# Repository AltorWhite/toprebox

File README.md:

topre ergo keyboard for my small hands

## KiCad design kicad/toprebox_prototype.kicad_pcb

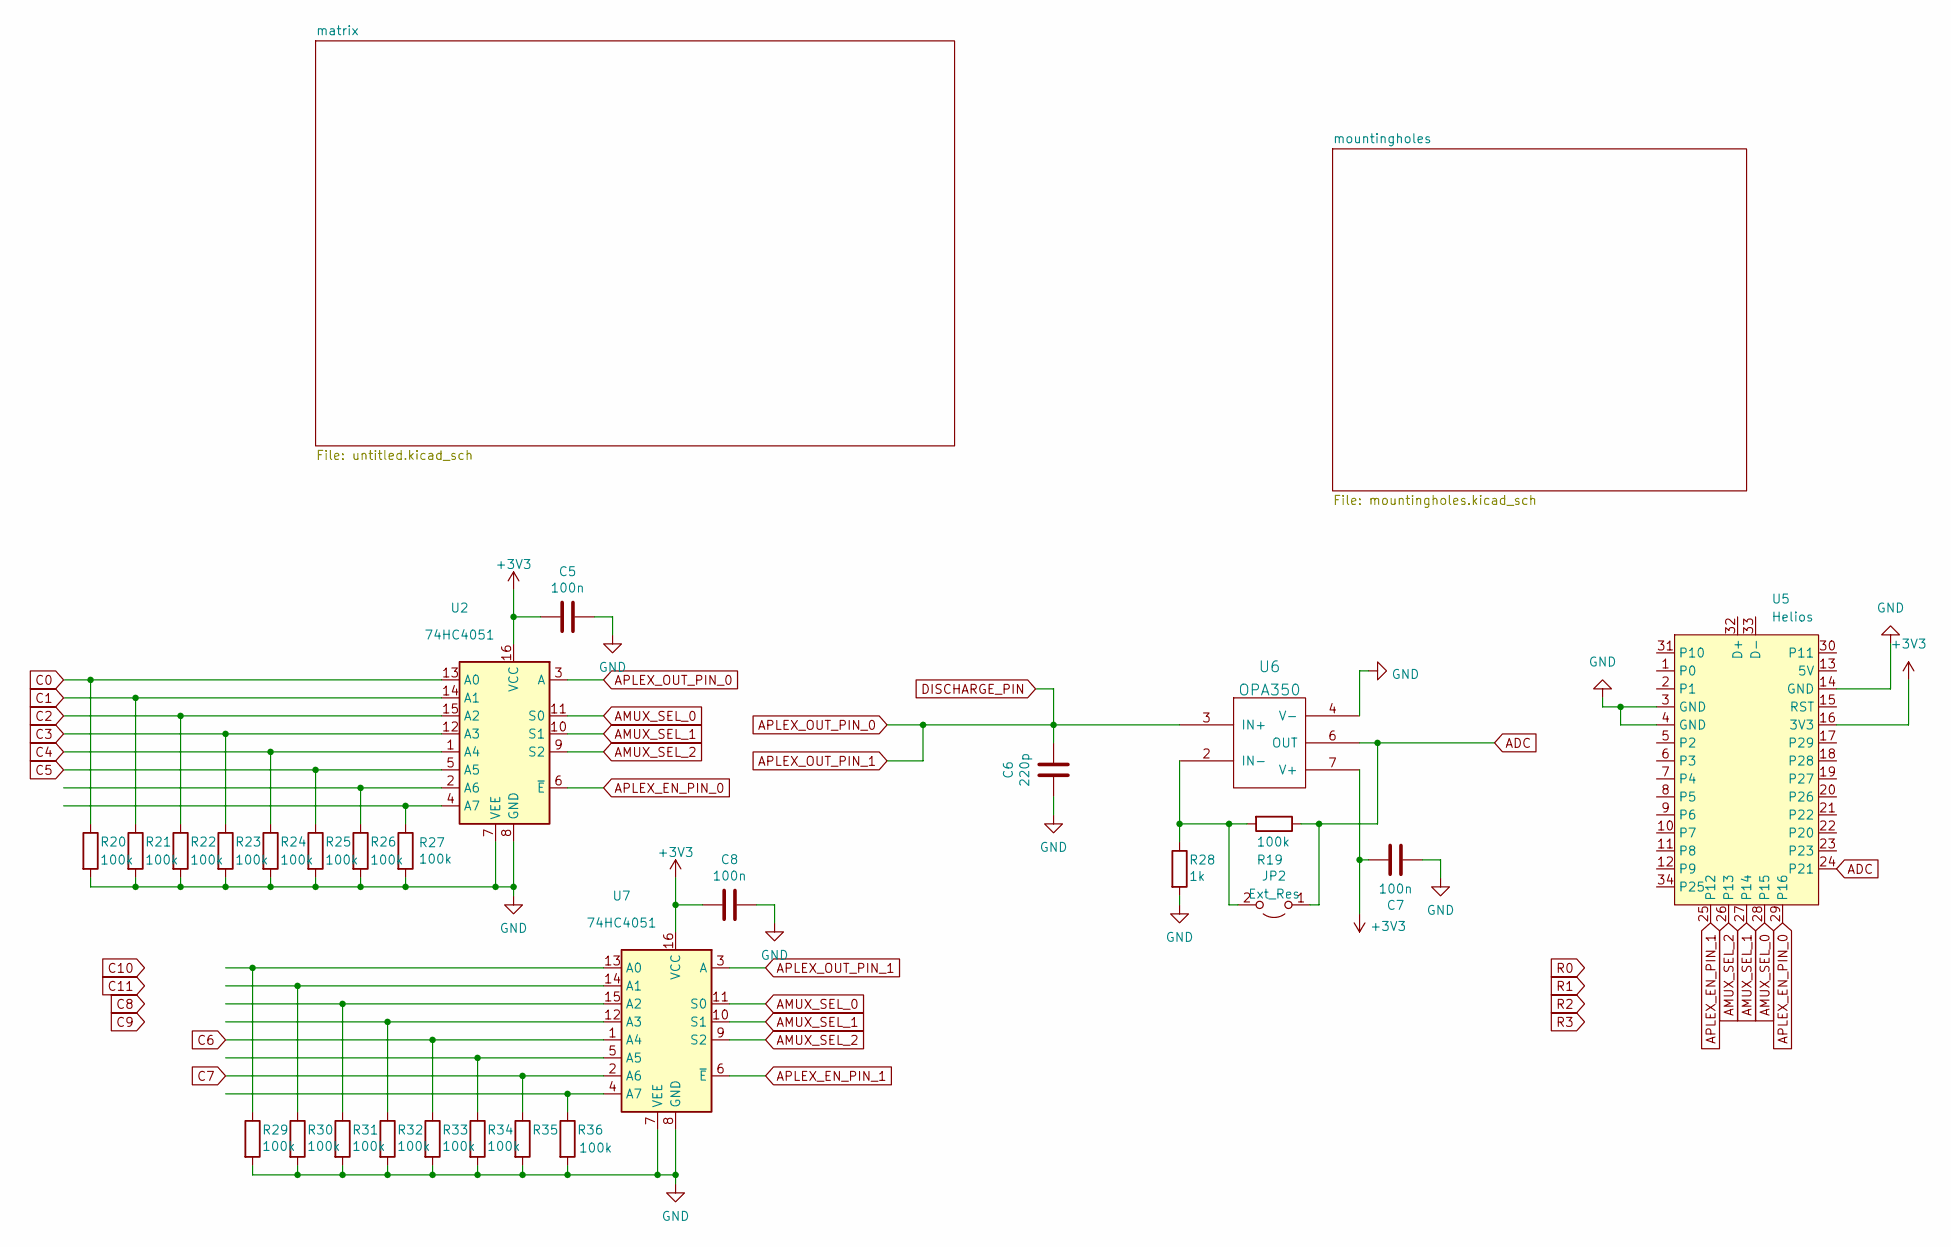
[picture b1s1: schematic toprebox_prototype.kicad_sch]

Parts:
C5, C7, C8: 100n; C_0402_1005Metric; LCSC C307331
C6: 220p; C_0402_1005Metric; LCSC C1530
JP2: Ext_Res; R_0603_1608Metric_Pad0.98x0.95mm_HandSolder
R19, R20, R21, R22, R23, R24, R25, R26, R27, R29, R30, R31, R32, R33, R34, R35, R36: 100k; R_0402_1005Metric; LCSC C25741
R28: 1k; R_0402_1005Metric; LCSC C11702
U2, U7: 74HC4051; TSSOP16; LCSC C5645
U5: Helios; RP2040_Pro_Micro
U6: OPA350; SOIC-8_3.9x4.9mm_P1.27mm; LCSC C13388

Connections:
+3V3: C5.2, C7.2, C8.2, U2.16 (VCC), U5.16 (3V3), U6.7 (V+), U7.16 (VCC)
ADC: JP2.1 (A), R19.1, U5.24 (P21), U6.6 (OUT)
AMUX_SEL_0: U2.11 (S0), U5.28 (P15), U7.11 (S0)
AMUX_SEL_1: U2.10 (S1), U5.27 (P14), U7.10 (S1)
AMUX_SEL_2: U2.9 (S2), U5.26 (P13), U7.9 (S2)
APLEX_EN_PIN_0: U2.6 (~E), U5.29 (P16)
APLEX_EN_PIN_1: U5.25 (P12), U7.6 (~E)
APLEX_OUT_PIN_0: C6.1, U2.3 (A), U6.3 (IN+), U7.3 (A)
C0: R20.1, U2.13 (A0); also elsewhere on the board
C1: R21.1, U2.14 (A1); also elsewhere on the board
C2: R22.1, U2.15 (A2); also elsewhere on the board
C3: R23.1, U2.12 (A3); also elsewhere on the board
C4: R24.1, U2.1 (A4); also elsewhere on the board
C5: R25.1, U2.5 (A5); also elsewhere on the board
C6: R33.1, U7.1 (A4); also elsewhere on the board
C7: R35.1, U7.2 (A6); also elsewhere on the board
GND: C5.1, C6.2, C7.1, C8.1, R20.2, R21.2, R22.2, R23.2, R24.2, R25.2, R26.2, R27.2, R28.2, R29.2, R30.2, R31.2, R32.2, R33.2, R34.2, R35.2, R36.2, U2.7 (VEE), U2.8 (GND), U5.3 (GND), U5.4 (GND), U5.14 (GND), U6.4 (V-), U7.7 (VEE), U7.8 (GND); also elsewhere on the board
unnamed: JP2.2 (B), R19.2, R28.1, U6.2 (IN-)
unnamed: R26.1, U2.2 (A6)
unnamed: R27.1, U2.4 (A7)
unnamed: R29.1, U7.13 (A0)
unnamed: R30.1, U7.14 (A1)
unnamed: R31.1, U7.15 (A2)
unnamed: R32.1, U7.12 (A3)
unnamed: R34.1, U7.5 (A5)
unnamed: R36.1, U7.4 (A7)

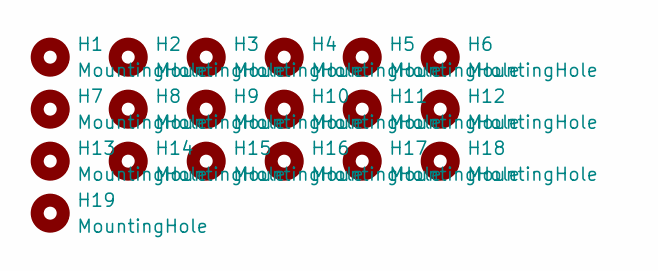
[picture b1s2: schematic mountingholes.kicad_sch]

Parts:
H1, H2, H3, H4, H5, H6, H7, H8, H9, H10, H11, H12, H13, H14, H15, H16, H17, H18, H19: MountingHole; HOLE_M2

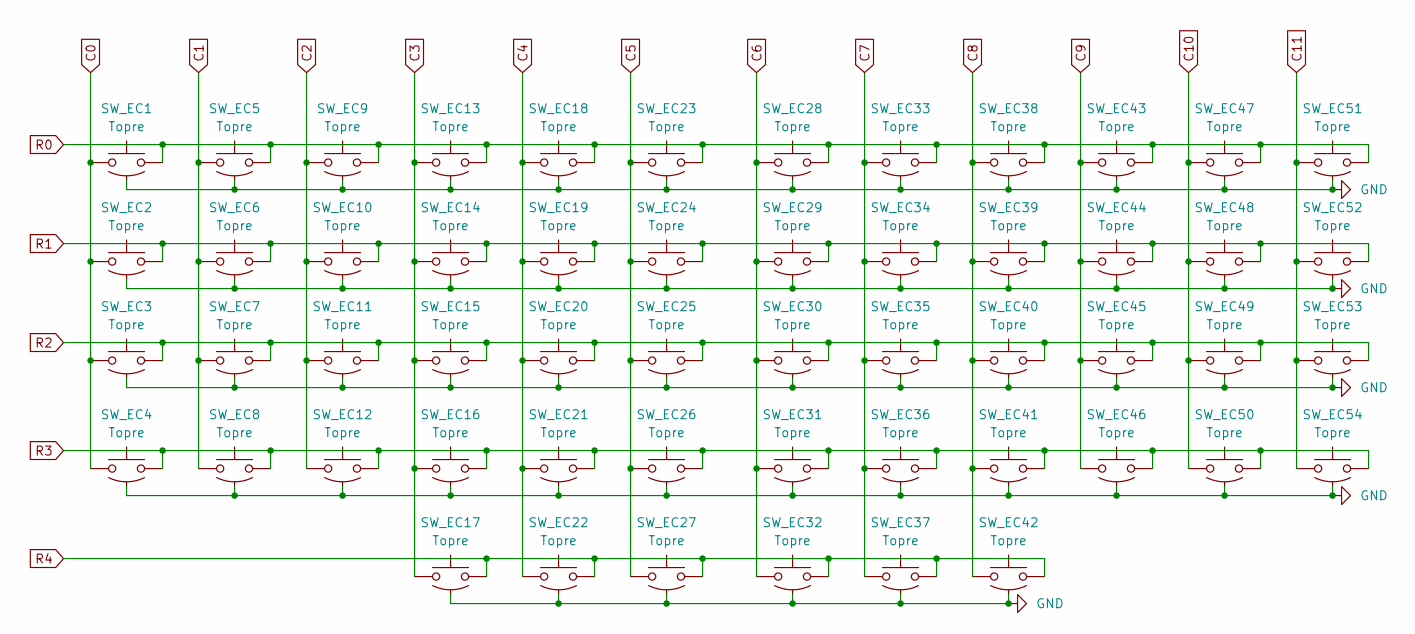
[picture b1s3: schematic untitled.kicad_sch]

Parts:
SW_EC1, SW_EC2, SW_EC3, SW_EC4, SW_EC5, SW_EC6, SW_EC7, SW_EC8, SW_EC9, SW_EC10, SW_EC11, SW_EC12, SW_EC13, SW_EC14, SW_EC15, SW_EC16, SW_EC17, SW_EC18, SW_EC19, SW_EC20, SW_EC21, SW_EC22, SW_EC23, SW_EC24, SW_EC25, SW_EC26, SW_EC27, SW_EC28, SW_EC29, SW_EC30, SW_EC31, SW_EC32, SW_EC33, SW_EC34, SW_EC35, SW_EC36, SW_EC37, SW_EC38, SW_EC39, SW_EC40, SW_EC41, SW_EC42, SW_EC43, SW_EC44, SW_EC45, SW_EC46, SW_EC47, SW_EC48, SW_EC49, SW_EC50, SW_EC51, SW_EC52, SW_EC53, SW_EC54: Topre

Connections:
C0: SW_EC1.2, SW_EC2.2, SW_EC3.2, SW_EC4.2; also elsewhere on the board
C1: SW_EC5.2, SW_EC6.2, SW_EC7.2, SW_EC8.2; also elsewhere on the board
C2: SW_EC9.2, SW_EC10.2, SW_EC11.2, SW_EC12.2; also elsewhere on the board
C3: SW_EC13.2, SW_EC14.2, SW_EC15.2, SW_EC16.2, SW_EC17.2; also elsewhere on the board
C4: SW_EC18.2, SW_EC19.2, SW_EC20.2, SW_EC21.2, SW_EC22.2; also elsewhere on the board
C5: SW_EC23.2, SW_EC24.2, SW_EC25.2, SW_EC26.2, SW_EC27.2; also elsewhere on the board
C6: SW_EC28.2, SW_EC29.2, SW_EC30.2, SW_EC31.2, SW_EC32.2; also elsewhere on the board
C7: SW_EC33.2, SW_EC34.2, SW_EC35.2, SW_EC36.2, SW_EC37.2; also elsewhere on the board
C8: SW_EC38.2, SW_EC39.2, SW_EC40.2, SW_EC41.2, SW_EC42.2
C9: SW_EC43.2, SW_EC44.2, SW_EC45.2, SW_EC46.2
C10: SW_EC47.2, SW_EC48.2, SW_EC49.2, SW_EC50.2
C11: SW_EC51.2, SW_EC52.2, SW_EC53.2, SW_EC54.2
GND: SW_EC1.3, SW_EC2.3, SW_EC3.3, SW_EC4.3, SW_EC5.3, SW_EC6.3, SW_EC7.3, SW_EC8.3, SW_EC9.3, SW_EC10.3, SW_EC11.3, SW_EC12.3, SW_EC13.3, SW_EC14.3, SW_EC15.3, SW_EC16.3, SW_EC17.3, SW_EC18.3, SW_EC19.3, SW_EC20.3, SW_EC21.3, SW_EC22.3, SW_EC23.3, SW_EC24.3, SW_EC25.3, SW_EC26.3, SW_EC27.3, SW_EC28.3, SW_EC29.3, SW_EC30.3, SW_EC31.3, SW_EC32.3, SW_EC33.3, SW_EC34.3, SW_EC35.3, SW_EC36.3, SW_EC37.3, SW_EC38.3, SW_EC39.3, SW_EC40.3, SW_EC41.3, SW_EC42.3, SW_EC43.3, SW_EC44.3, SW_EC45.3, SW_EC46.3, SW_EC47.3, SW_EC48.3, SW_EC49.3, SW_EC50.3, SW_EC51.3, SW_EC52.3, SW_EC53.3, SW_EC54.3; also elsewhere on the board
R0: SW_EC1.1, SW_EC5.1, SW_EC9.1, SW_EC13.1, SW_EC18.1, SW_EC23.1, SW_EC28.1, SW_EC33.1, SW_EC38.1, SW_EC43.1, SW_EC47.1, SW_EC51.1
R1: SW_EC2.1, SW_EC6.1, SW_EC10.1, SW_EC14.1, SW_EC19.1, SW_EC24.1, SW_EC29.1, SW_EC34.1, SW_EC39.1, SW_EC44.1, SW_EC48.1, SW_EC52.1
R2: SW_EC3.1, SW_EC7.1, SW_EC11.1, SW_EC15.1, SW_EC20.1, SW_EC25.1, SW_EC30.1, SW_EC35.1, SW_EC40.1, SW_EC45.1, SW_EC49.1, SW_EC53.1
R3: SW_EC4.1, SW_EC8.1, SW_EC12.1, SW_EC16.1, SW_EC21.1, SW_EC26.1, SW_EC31.1, SW_EC36.1, SW_EC41.1, SW_EC46.1, SW_EC50.1, SW_EC54.1
R4: SW_EC17.1, SW_EC22.1, SW_EC27.1, SW_EC32.1, SW_EC37.1, SW_EC42.1

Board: 2 copper layers, 127 parts (100 on the bottom side), 35 nets, no tracks yet.

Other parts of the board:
S28, S29, S30, S31, S32, S33, S34, S35, S36, S37, S38, S39, S40, S41, S42, S43, S44, S45, S46, S47, S48, S49, S50, S51, S52, S53, S54: Topre

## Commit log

2025-01-29 ergogen
2025-01-29 kicad prototype
2025-01-30 completed matrix
2025-01-31 replaced half of the matrix
2025-02-01 something
2025-02-01 matrix complete
2025-02-03 stuff
2025-02-06 better splay and stagger
2025-02-06 larger thumb cluster
2025-02-11 potential new layout
2025-02-14 new plate outline
2025-02-14 re did the pcb
